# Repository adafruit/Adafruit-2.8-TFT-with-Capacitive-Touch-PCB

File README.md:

## Adafruit 2.8 TFT with Capacitive Touch PCB
<a href="http://www.adafruit.com/products/2090"><br/>
Click here to purchase one from the Adafruit shop</a>

Add some jazz & pizazz to your project with a color capactive touchscreen LCD. This TFT display is big (2.8" diagonal) bright (4 white-LED backlight) and colorful! 240x320 pixels with individual RGB pixel control, this has way more resolution than a black and white 128x64 display. As a bonus, this display has a capacitive single-touch touchscreen attached to it already, so you can detect finger presses anywhere on the screen. (We also have a resistive touchscreen version of this display breakout)

This display has a controller built into it with RAM buffering, so that almost no work is done by the microcontroller. The display can be used in two modes: 8-bit and SPI. For 8-bit mode, you'll need 8 digital data lines and 4 or 5 digital control lines to read and write to the display (12 lines total). SPI mode requires only 5 pins total (SPI data in, data out, clock, select, and d/c) but is slower than 8-bit mode. In addition, 2 I2C pins are required for the touch screen controller.

We wrapped up this display into an easy-to-use breakout board, with SPI connections on one end and 8-bit on the other. Both are 3-5V compliant with high-speed level shifters so you can use with any microcontroller. If you're going with SPI mode, you can also take advantage of the onboard MicroSD card socket to display images. (The microSD card not included, but any will work).

PCB files for the Adafruit 2.8" TFT with Capacitive Touch PCB. The format is EagleCAD schematic and board layout
- https://www.adafruit.com/products/2090

### License

Adafruit invests time and resources providing this open source design, please support Adafruit and open-source hardware by purchasing products from [Adafruit](https://www.adafruit.com)!

All text above must be included in any redistribution

Designed by Limor Fried/Ladyada for Adafruit Industries.
Creative Commons Attribution/Share-Alike, all text above must be included in any redistribution. 
See license.txt for additional information.

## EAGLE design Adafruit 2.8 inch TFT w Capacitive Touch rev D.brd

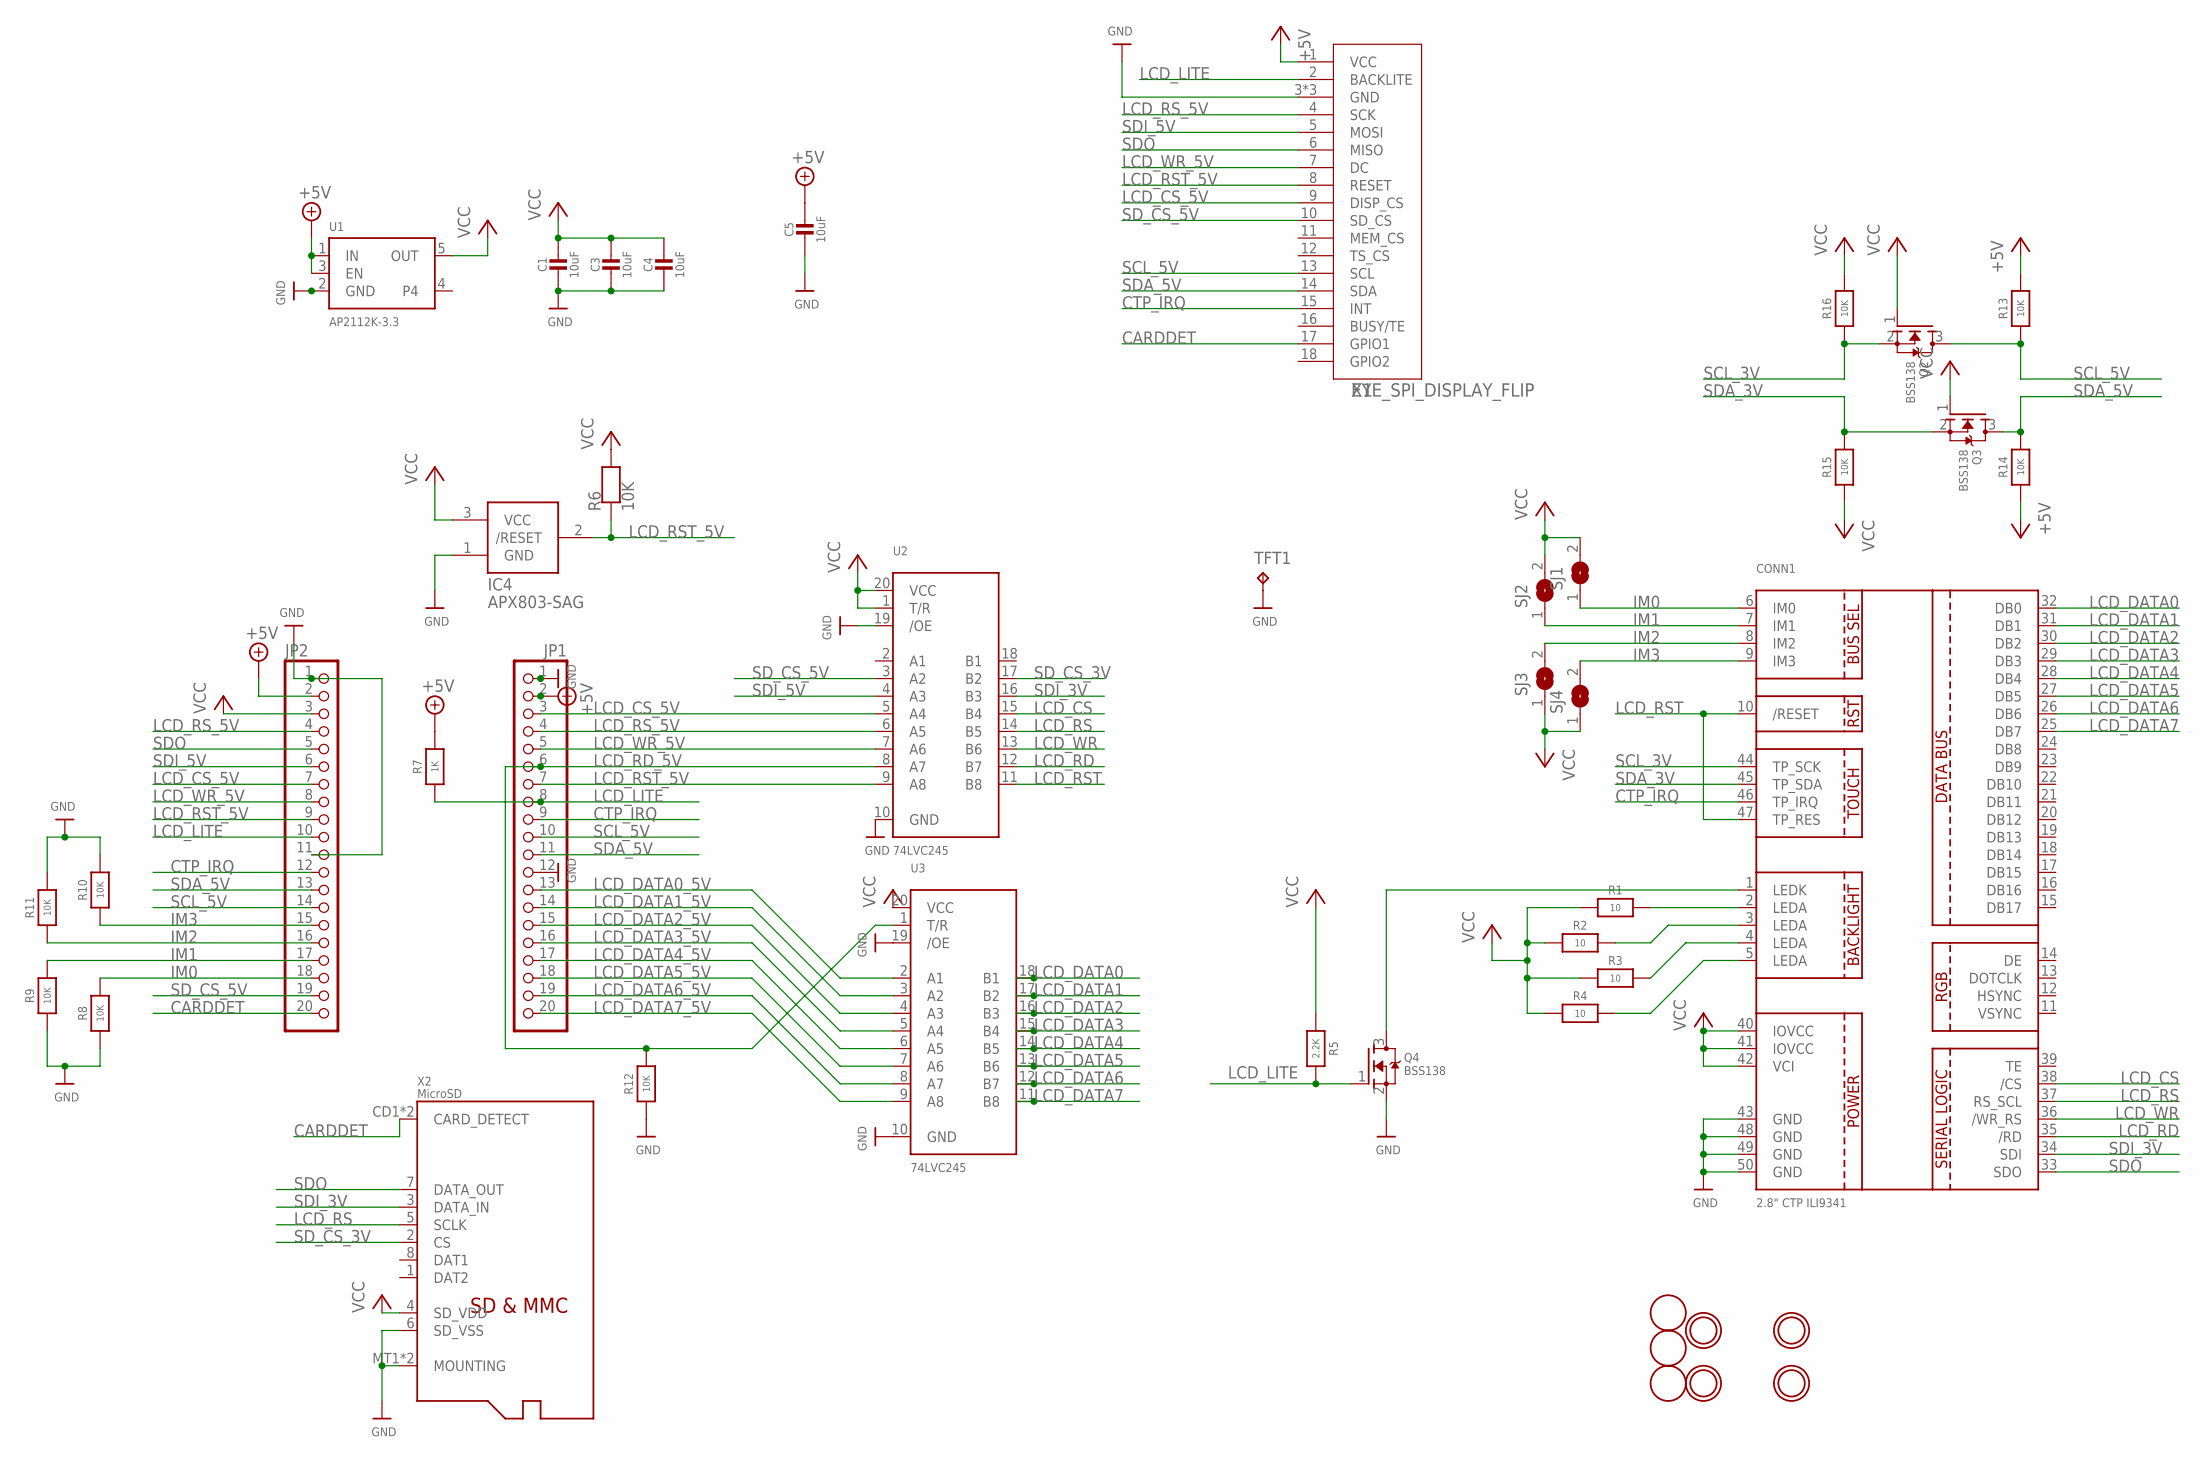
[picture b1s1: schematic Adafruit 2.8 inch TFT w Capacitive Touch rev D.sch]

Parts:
C1, C3, C4, C5: 10uF; 0805-NO
CONN1: 2.8" CTP ILI9341; TFT_2.83IN_240X320_50PIN
IC4: APX803-SAG; SOT23-WIDE
JP1, JP2: HEADER-1X20ROUND; 1X20_ROUND
Q2, Q3, Q4: BSS138; SOT23-WIDE
R1, R2, R3, R4: 10; 0603-NO
R5: 2.2K; 0603-NO
R6, R8, R9, R10, R11, R12, R13, R14, R15, R16: 10K; 0603-NO
R7: 1K; 0603-NO
SJ1, SJ2, SJ3, SJ4: SOLDERJUMPER; SOLDERJUMPER_ARROW_NOPASTE
TFT1: 2.8in CTP TFT; TP06R
U1: AP2112K-3.3; SOT23-5; JLC_ROTATION 0
U2, U3: 74LVC245; TSSOP20
U$7, U$15, U$16, U$17: MOUNTINGHOLE3.0THIN; MOUNTINGHOLE_3.0_PLATEDTHIN
U$9, U$11, U$23: FIDUCIAL; FIDUCIAL_1MM
X1: EYE_SPI_DISPLAY_FLIP; EYE_SPI_DISPLAY_BOTCONTACT
X2: MicroSD; MICROSD

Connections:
+5V: C5.1, JP1.2, JP2.2, R7.2, R13.2, R14.1, U1.1 (IN), U1.3 (EN), X1.1 (VCC)
CARDDET: JP2.20, X1.17 (GPIO1), X2.CD1 (CARD_DETECT), X2.CD2 (CARD_DETECT)
CTP_IRQ: CONN1.46 (TP_IRQ), JP1.9, JP2.12, X1.15 (INT)
GND: C1.2, C3.2, C4.2, C5.2, CONN1.43 (GND), CONN1.48 (GND), CONN1.49 (GND), CONN1.50 (GND), IC4.1 (GND), JP1.1, JP1.12, JP2.1, JP2.11, Q4.2 (S), R8.1, R9.1, R10.2, R11.2, R12.1, TFT1.TP, U1.2 (GND), U2.10 (GND), U2.19 (/OE), U3.10 (GND), U3.19 (/OE), X1.3 (GND), X1.SUPPORT1 (GND), X1.SUPPORT2 (GND), X2.6 (SD_VSS), X2.MT1 (MOUNTING), X2.MT2 (MOUNTING)
IM0: CONN1.6 (IM0), JP2.18, R8.2, SJ1.1
IM1: CONN1.7 (IM1), JP2.17, R9.2, SJ2.1
IM2: CONN1.8 (IM2), JP2.16, R11.1, SJ3.2
IM3: CONN1.9 (IM3), JP2.15, R10.1, SJ4.2
LCD_CS: CONN1.38 (/CS), U2.15 (B4)
LCD_CS_5V: JP1.3, JP2.7, U2.5 (A4), X1.9 (DISP_CS)
LCD_DATA0: CONN1.32 (DB0), U3.18 (B1)
LCD_DATA0_5V: JP1.13, U3.2 (A1)
LCD_DATA1: CONN1.31 (DB1), U3.17 (B2)
LCD_DATA1_5V: JP1.14, U3.3 (A2)
LCD_DATA2: CONN1.30 (DB2), U3.16 (B3)
LCD_DATA2_5V: JP1.15, U3.4 (A3)
LCD_DATA3: CONN1.29 (DB3), U3.15 (B4)
LCD_DATA3_5V: JP1.16, U3.5 (A4)
LCD_DATA4: CONN1.28 (DB4), U3.14 (B5)
LCD_DATA4_5V: JP1.17, U3.6 (A5)
LCD_DATA5: CONN1.27 (DB5), U3.13 (B6)
LCD_DATA5_5V: JP1.18, U3.7 (A6)
LCD_DATA6: CONN1.26 (DB6), U3.12 (B7)
LCD_DATA6_5V: JP1.19, U3.8 (A7)
LCD_DATA7: CONN1.25 (DB7), U3.11 (B8)
LCD_DATA7_5V: JP1.20, U3.9 (A8)
LCD_LITE: JP1.8, JP2.10, Q4.1 (G), R5.2, R7.1, X1.2 (BACKLITE)
LCD_RD: CONN1.35 (/RD), U2.12 (B7)
LCD_RD_5V: JP1.6, R12.2, U2.8 (A7), U3.1 (T/R)
LCD_RS: CONN1.37 (RS_SCL), U2.14 (B5), X2.5 (SCLK)
LCD_RST: CONN1.10 (/RESET), CONN1.47 (TP_RES), U2.11 (B8)
LCD_RST_5V: IC4.2 (/RESET), JP1.7, JP2.9, R6.1, U2.9 (A8), X1.8 (RESET)
LCD_RS_5V: JP1.4, JP2.4, U2.6 (A5), X1.4 (SCK)
LCD_WR: CONN1.36 (/WR_RS), U2.13 (B6)
LCD_WR_5V: JP1.5, JP2.8, U2.7 (A6), X1.7 (DC)
unnamed: CONN1.5 (LEDA), R4.2
unnamed: CONN1.2 (LEDA), R1.2
unnamed: CONN1.3 (LEDA), R2.2
unnamed: CONN1.4 (LEDA), R3.2
unnamed: CONN1.1 (LEDK), Q4.3 (D)
SCL_3V: CONN1.44 (TP_SCK), Q2.2 (S), R16.1
SCL_5V: JP1.10, JP2.14, Q2.3 (D), R13.1, X1.13 (SCL)
SDA_3V: CONN1.45 (TP_SDA), Q3.2 (S), R15.2
SDA_5V: JP1.11, JP2.13, Q3.3 (D), R14.2, X1.14 (SDA)
SDI_3V: CONN1.34 (SDI), U2.16 (B3), X2.3 (DATA_IN)
SDI_5V: JP2.6, U2.4 (A3), X1.5 (MOSI)
SDO: CONN1.33 (SDO), JP2.5, X1.6 (MISO), X2.7 (DATA_OUT)
SD_CS_3V: U2.17 (B2), X2.2 (CS)
SD_CS_5V: JP2.19, U2.3 (A2), X1.10 (SD_CS)
VCC: C1.1, C3.1, C4.1, CONN1.40 (IOVCC), CONN1.41 (IOVCC), CONN1.42 (VCI), IC4.3 (VCC), JP2.3, Q2.1 (G), Q3.1 (G), R1.1, R2.1, R3.1, R4.1, R5.1, R6.2, R15.1, R16.2, SJ1.2, SJ2.2, SJ3.1, SJ4.1, U1.5 (OUT), U2.1 (T/R), U2.20 (VCC), U3.20 (VCC), X2.4 (SD_VDD)

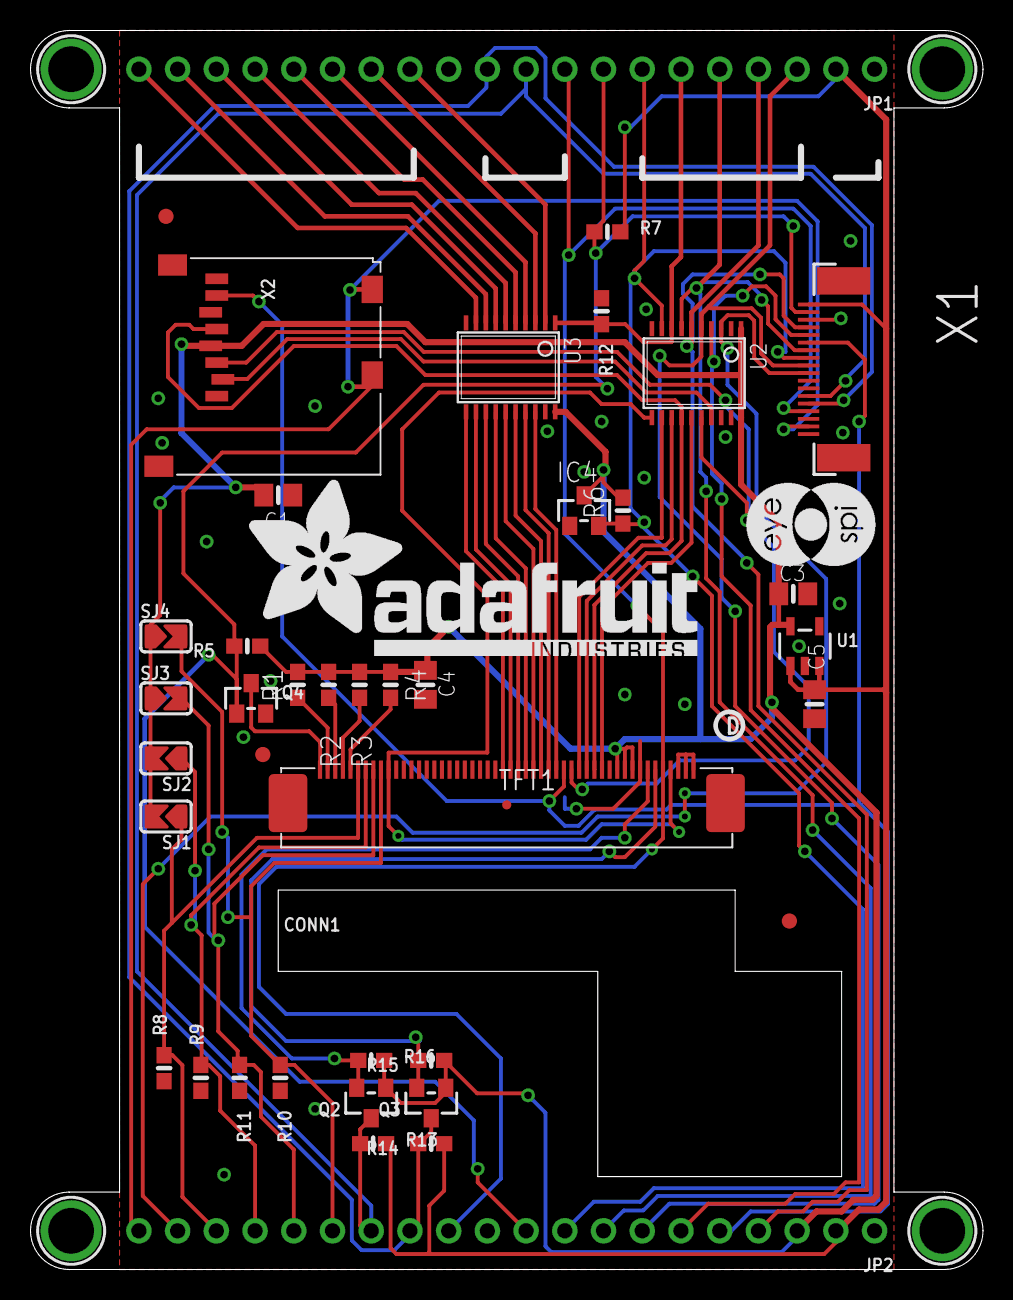
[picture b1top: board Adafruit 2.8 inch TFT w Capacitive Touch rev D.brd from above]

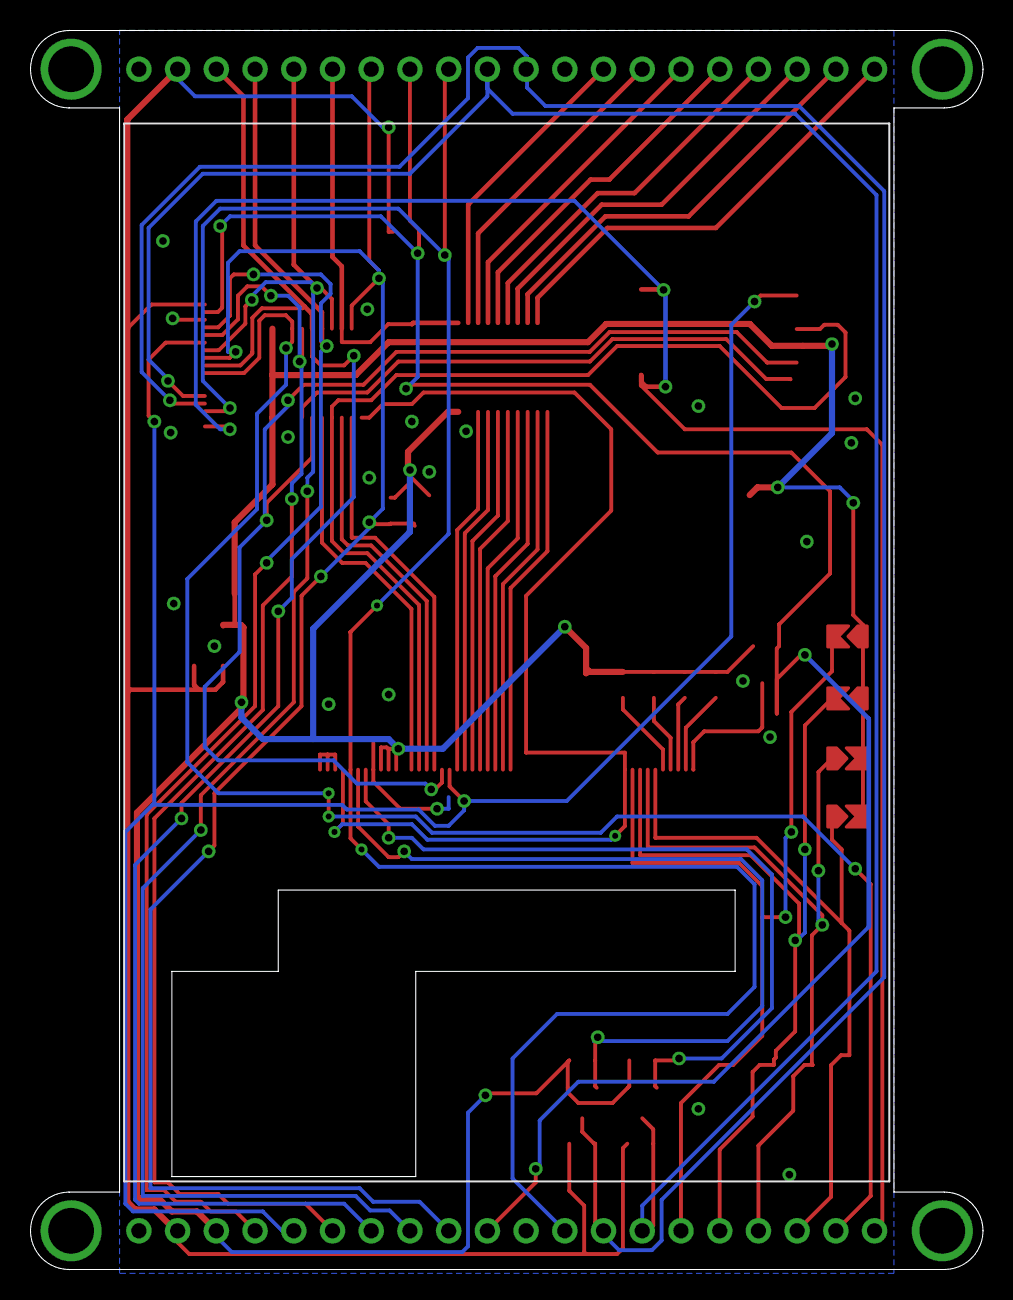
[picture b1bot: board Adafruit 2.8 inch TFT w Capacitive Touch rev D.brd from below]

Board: 2 copper layers, 62.5 x 81.3 mm, 144 parts (41 on the bottom side), 50 nets.

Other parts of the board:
PLABEL0: PLABEL0
PLABEL1: PLABEL1
PLABEL2: PLABEL2
PLABEL3: PLABEL3
PLABEL4: PLABEL4
PLABEL5: PLABEL5
PLABEL6: PLABEL6
PLABEL7: PLABEL7
PLABEL8: PLABEL8
PLABEL9: PLABEL9
PLABEL10: PLABEL10
PLABEL11: PLABEL11
PLABEL12: PLABEL12
PLABEL13: PLABEL13
PLABEL14: PLABEL14
PLABEL15: PLABEL15
PLABEL16: PLABEL16
PLABEL17: PLABEL17
PLABEL18: PLABEL18
PLABEL19: PLABEL19
PLABEL20: PLABEL20
PLABEL21: PLABEL21
PLABEL22: PLABEL22
PLABEL23: PLABEL23
PLABEL24: PLABEL24
PLABEL25: PLABEL25
PLABEL26: PLABEL26
PLABEL27: PLABEL27
PLABEL28: PLABEL28
PLABEL29: PLABEL29
PLABEL30: PLABEL30
PLABEL31: PLABEL31
PLABEL32: PLABEL32
PLABEL33: PLABEL33
PLABEL34: PLABEL34
PLABEL35: PLABEL35
PLABEL36: PLABEL36
PLABEL37: PLABEL37
PLABEL38: PLABEL38
PLABEL39: PLABEL39
PLABEL40: PLABEL40
PLABEL41: PLABEL41
PLABEL42: PLABEL42
PLABEL43: PLABEL43
PLABEL44: PLABEL44
PLABEL45: PLABEL45
PLABEL46: PLABEL46
PLABEL47: PLABEL47
PLABEL48: PLABEL48
PLABEL49: PLABEL49
PLABEL50: PLABEL50
PLABEL51: PLABEL51
PLABEL52: PLABEL52
PLABEL53: PLABEL53
PLABEL54: PLABEL54
PLABEL55: PLABEL55
PLABEL56: PLABEL56
PLABEL57: PLABEL57
PLABEL58: PLABEL58
PLABEL59: PLABEL59
PLABEL60: PLABEL60
PLABEL61: PLABEL61
PLABEL62: PLABEL62
PLABEL63: PLABEL63
PLABEL64: PLABEL64
PLABEL65: PLABEL65
PLABEL66: PLABEL66
PLABEL67: PLABEL67
PLABEL68: PLABEL68
PLABEL69: PLABEL69
PLABEL70: PLABEL70
PLABEL71: PLABEL71
PLABEL72: PLABEL72
PLABEL73: PLABEL73
PLABEL74: PLABEL74
PLABEL75: PLABEL75
PLABEL76: PLABEL76
PLABEL77: PLABEL77
PLABEL78: PLABEL78
PLABEL79: PLABEL79
PLABEL80: PLABEL80
PLABEL81: PLABEL81
PLABEL82: PLABEL82
PLABEL83: PLABEL83
PLABEL84: PLABEL84
PLABEL85: PLABEL85
PLABEL86: PLABEL86
PLABEL87: PLABEL87
PLABEL88: PLABEL88
PLABEL89: PLABEL89
PLABEL90: PLABEL90
PLABEL91: PLABEL91
PLABEL92: PLABEL92
PLABEL93: PLABEL93
PLABEL94: PLABEL94
PLABEL95: PLABEL95
PLABEL96: PLABEL96
U$19: ADAFRUIT_TEXT_30MM
U$28: PCBFEAT-REV-040
U$29: EYESPI_MINI_LOGO

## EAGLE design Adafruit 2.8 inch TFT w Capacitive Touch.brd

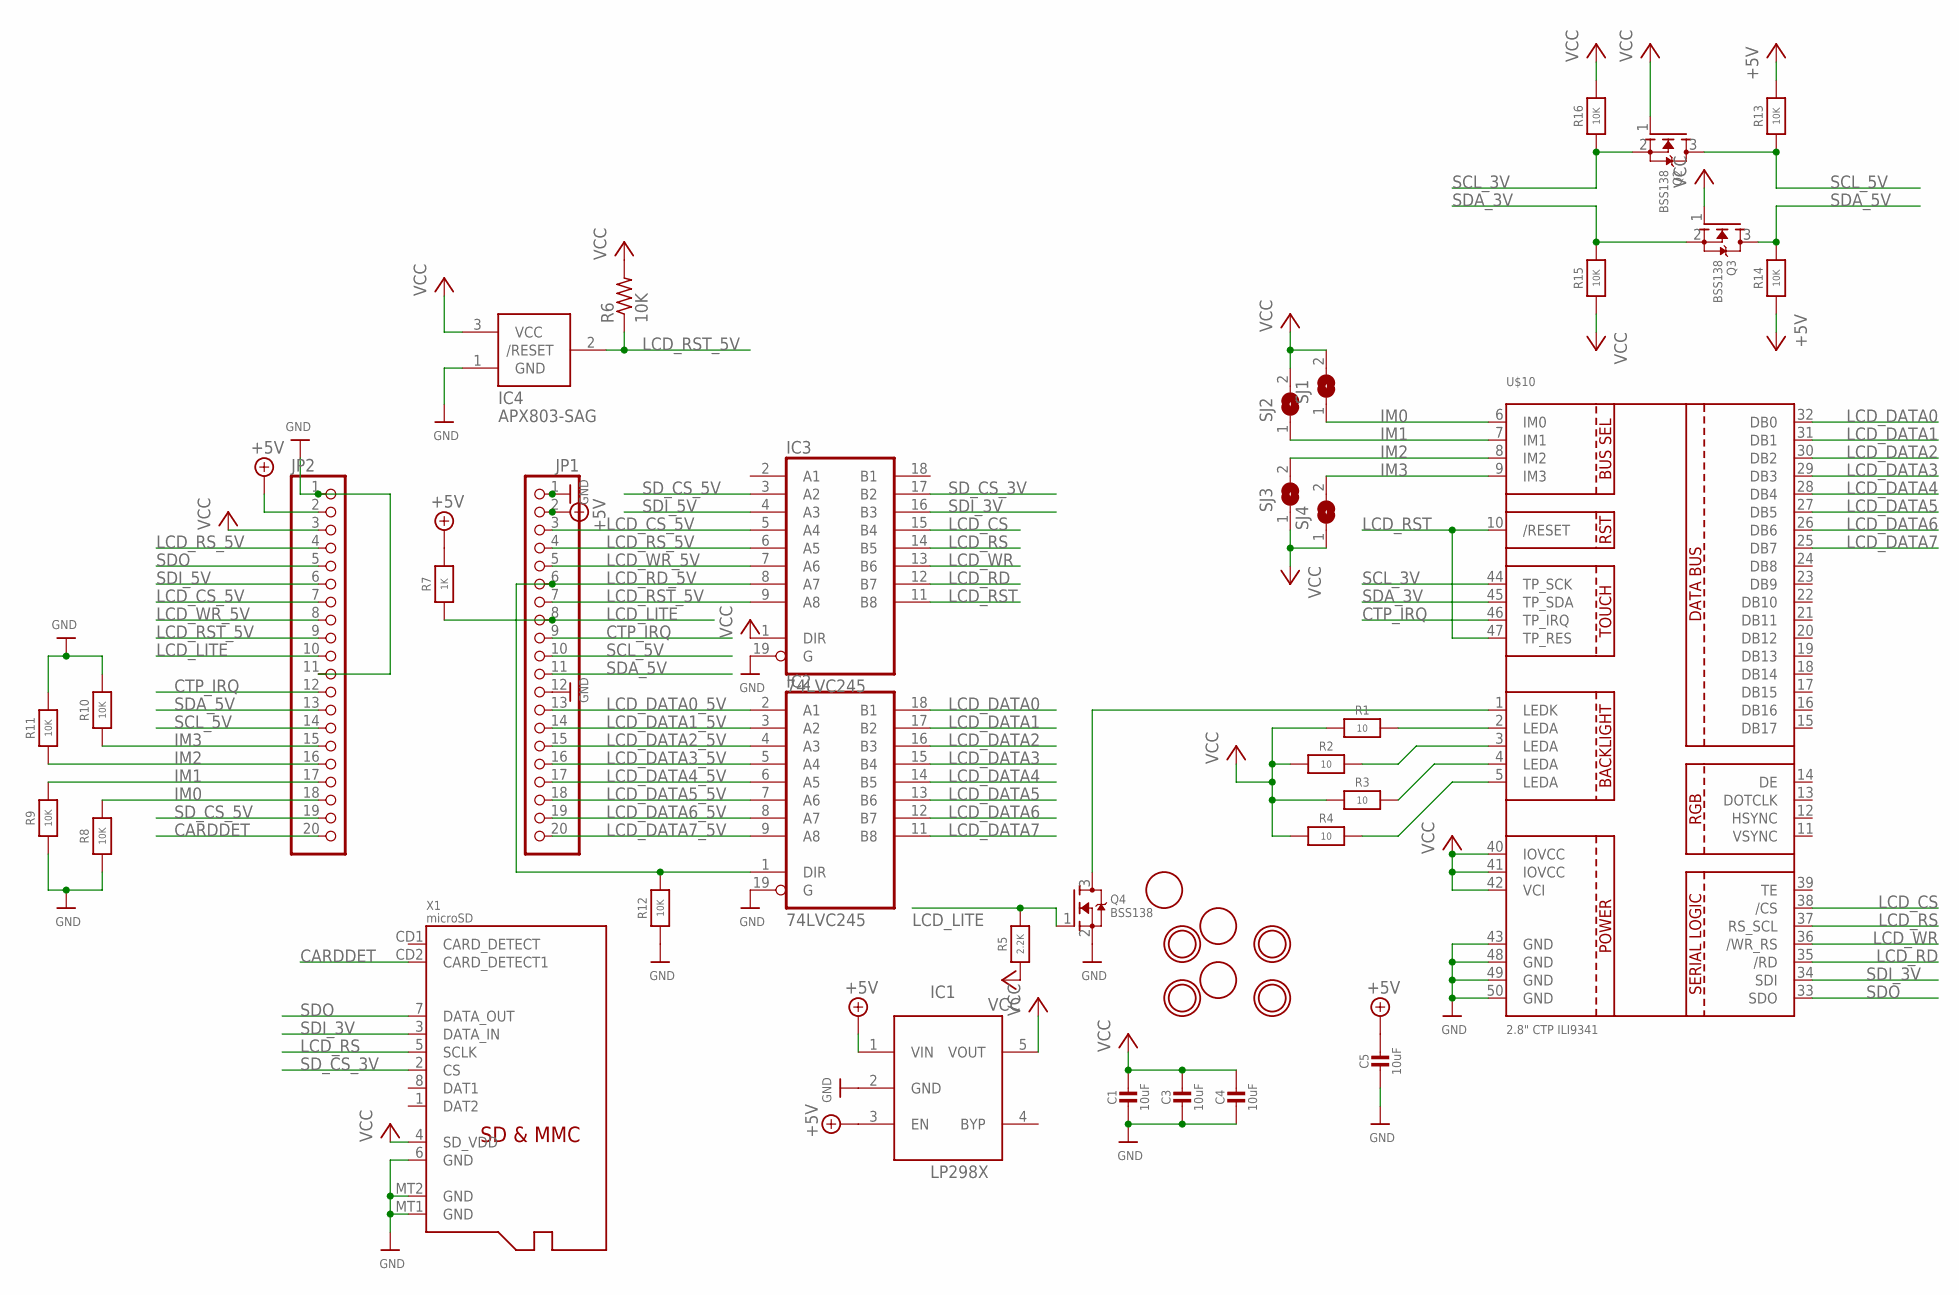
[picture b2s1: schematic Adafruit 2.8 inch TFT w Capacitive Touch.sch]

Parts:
C1, C3, C4, C5: 10uF; 0805-NO
IC1: MIC5225-3.3; SOT23-5L
IC2, IC3: 74LVC245; SO20W
IC4: APX803-SAG; SOT23
JP1, JP2: HEADER-1X20ROUND; 1X20_ROUND
Q2, Q3, Q4: BSS138; SOT23-WIDE
R1, R2, R3, R4: 10; 0805-NO
R5: 2.2K; 0805-NO
R6: 10K; R0805
R7: 1K; 0805-NO
R8, R9, R10, R11, R12, R13, R14, R15, R16: 10K; 0805-NO
SJ1, SJ2, SJ3, SJ4: SOLDERJUMPER; SOLDERJUMPER_ARROW_NOPASTE
U$7, U$15, U$16, U$17: MOUNTINGHOLE3.0THIN; MOUNTINGHOLE_3.0_PLATEDTHIN
U$9, U$11, U$23: FIDUCIAL; FIDUCIAL_1MM
U$10: 2.8" CTP ILI9341; TFT_2.83IN_240X320_50PIN
X1: microSD; MICROSD

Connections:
+5V: C5.1, IC1.1 (VIN), IC1.3 (EN), JP1.2, JP2.2, R7.2, R13.2, R14.1
CARDDET: JP2.20, X1.CD2 (CARD_DETECT1)
CTP_IRQ: JP1.9, JP2.12, U$10.46 (TP_IRQ)
GND: C1.2, C3.2, C4.2, C5.2, IC1.2 (GND), IC2.10 (GND), IC2.19 (G), IC3.10 (GND), IC3.19 (G), IC4.1 (GND), JP1.1, JP1.12, JP2.1, JP2.11, Q4.2 (S), R8.1, R9.1, R10.2, R11.2, R12.1, U$10.43 (GND), U$10.48 (GND), U$10.49 (GND), U$10.50 (GND), X1.6 (GND), X1.MT1 (GND), X1.MT2 (GND)
IM0: JP2.18, R8.2, SJ1.1, U$10.6 (IM0)
IM1: JP2.17, R9.2, SJ2.1, U$10.7 (IM1)
IM2: JP2.16, R11.1, SJ3.2, U$10.8 (IM2)
IM3: JP2.15, R10.1, SJ4.2, U$10.9 (IM3)
LCD_CS: IC3.15 (B4), U$10.38 (/CS)
LCD_CS_5V: IC3.5 (A4), JP1.3, JP2.7
LCD_DATA0: IC2.18 (B1), U$10.32 (DB0)
LCD_DATA0_5V: IC2.2 (A1), JP1.13
LCD_DATA1: IC2.17 (B2), U$10.31 (DB1)
LCD_DATA1_5V: IC2.3 (A2), JP1.14
LCD_DATA2: IC2.16 (B3), U$10.30 (DB2)
LCD_DATA2_5V: IC2.4 (A3), JP1.15
LCD_DATA3: IC2.15 (B4), U$10.29 (DB3)
LCD_DATA3_5V: IC2.5 (A4), JP1.16
LCD_DATA4: IC2.14 (B5), U$10.28 (DB4)
LCD_DATA4_5V: IC2.6 (A5), JP1.17
LCD_DATA5: IC2.13 (B6), U$10.27 (DB5)
LCD_DATA5_5V: IC2.7 (A6), JP1.18
LCD_DATA6: IC2.12 (B7), U$10.26 (DB6)
LCD_DATA6_5V: IC2.8 (A7), JP1.19
LCD_DATA7: IC2.11 (B8), U$10.25 (DB7)
LCD_DATA7_5V: IC2.9 (A8), JP1.20
LCD_LITE: JP1.8, JP2.10, Q4.1 (G), R5.2, R7.1
LCD_RD: IC3.12 (B7), U$10.35 (/RD)
LCD_RD_5V: IC2.1 (DIR), IC3.8 (A7), JP1.6, R12.2
LCD_RS: IC3.14 (B5), U$10.37 (RS_SCL), X1.5 (SCLK)
LCD_RST: IC3.11 (B8), U$10.10 (/RESET), U$10.47 (TP_RES)
LCD_RST_5V: IC3.9 (A8), IC4.2 (/RESET), JP1.7, JP2.9, R6.1
LCD_RS_5V: IC3.6 (A5), JP1.4, JP2.4
LCD_WR: IC3.13 (B6), U$10.36 (/WR_RS)
LCD_WR_5V: IC3.7 (A6), JP1.5, JP2.8
unnamed: R4.2, U$10.5 (LEDA)
unnamed: R1.2, U$10.2 (LEDA)
unnamed: R2.2, U$10.3 (LEDA)
unnamed: R3.2, U$10.4 (LEDA)
unnamed: Q4.3 (D), U$10.1 (LEDK)
SCL_3V: Q2.2 (S), R16.1, U$10.44 (TP_SCK)
SCL_5V: JP1.10, JP2.14, Q2.3 (D), R13.1
SDA_3V: Q3.2 (S), R15.2, U$10.45 (TP_SDA)
SDA_5V: JP1.11, JP2.13, Q3.3 (D), R14.2
SDI_3V: IC3.16 (B3), U$10.34 (SDI), X1.3 (DATA_IN)
SDI_5V: IC3.4 (A3), JP2.6
SDO: JP2.5, U$10.33 (SDO), X1.7 (DATA_OUT)
SD_CS_3V: IC3.17 (B2), X1.2 (CS)
SD_CS_5V: IC3.3 (A2), JP2.19
VCC: C1.1, C3.1, C4.1, IC1.5 (VOUT), IC2.20 (VCC), IC3.1 (DIR), IC3.20 (VCC), IC4.3 (VCC), JP2.3, Q2.1 (G), Q3.1 (G), R1.1, R2.1, R3.1, R4.1, R5.1, R6.2, R15.1, R16.2, SJ1.2, SJ2.2, SJ3.1, SJ4.1, U$10.40 (IOVCC), U$10.41 (IOVCC), U$10.42 (VCI), X1.4 (SD_VDD)

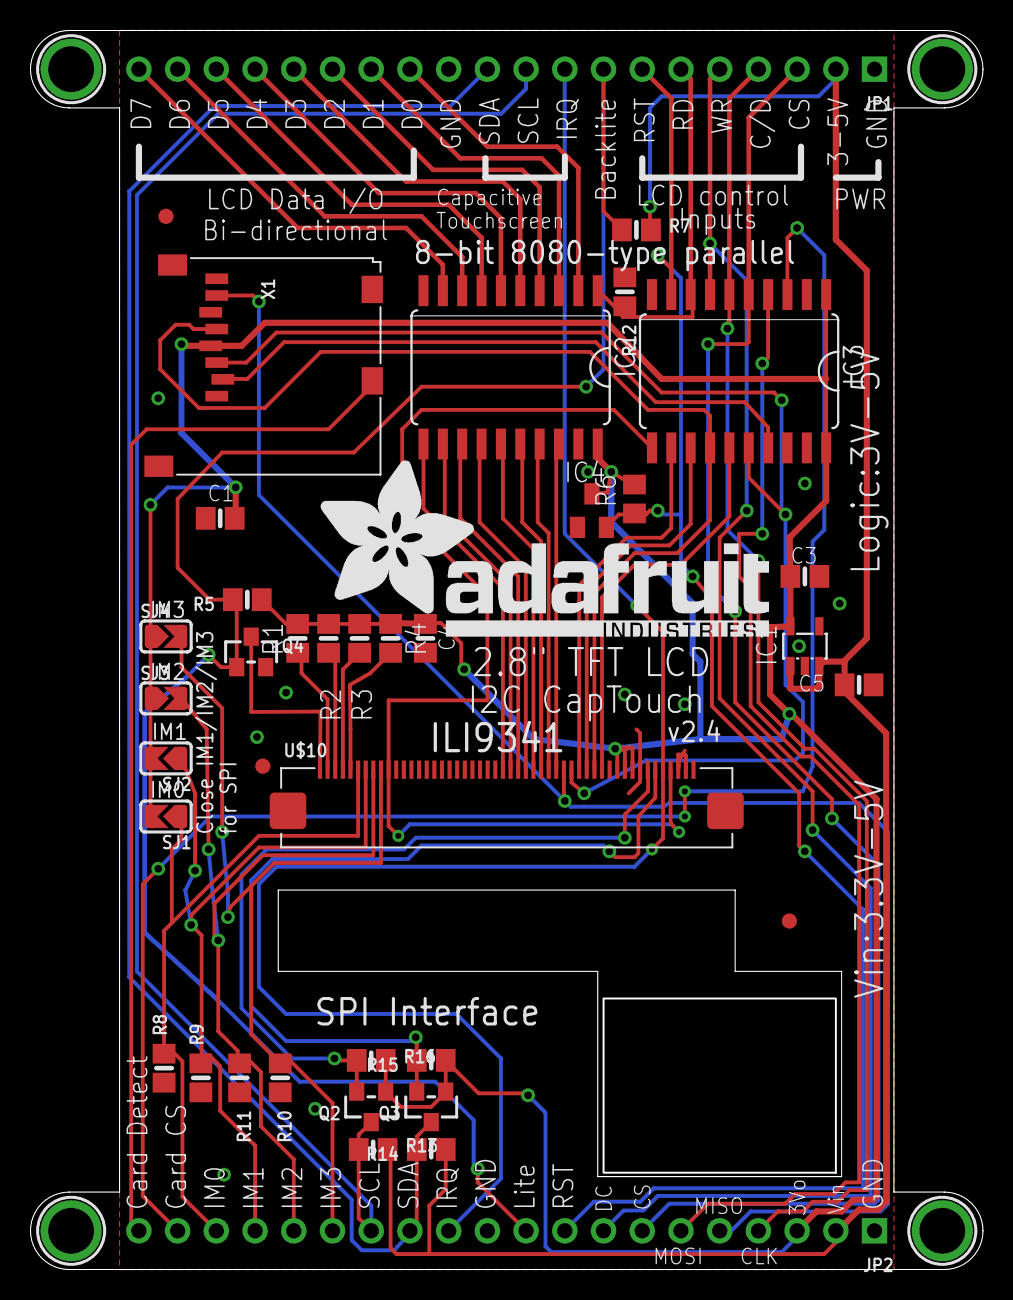
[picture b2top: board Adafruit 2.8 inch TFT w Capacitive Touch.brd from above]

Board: 2 copper layers, 62.5 x 81.3 mm, 43 parts (1 on the bottom side), 50 nets.

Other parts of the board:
U$19: ADAFRUIT_TEXT_30MM

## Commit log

2016-08-03 init
2026-01-05 adding rev d files
    resolves https://github.com/adafruit/Adafruit-2.8-TFT-with-Capacitive-Touch-PCB/issues/2
